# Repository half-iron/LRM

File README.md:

# LRM übersicht

### Ordner

- `axle_sensors` achsensoren info und firmware
- `NTiXL2` entält die python implementierung der serielle schnittstelle zur XL2 messgerät. Diesem Modul  
- `pyLRM` entält den python code notwendig für die scripts.

### Scripts

Die scripts dienen zur Bedienung der Messanlage. Die Scripts implementieren eine rehie von 
funktionen. Den Befehl `python3 scriptname.py -h` gibt Hinweise über die funktionalität und
 Anwendug der Scripts. 
 
Ein übersicht der implementierten funktionalitäten sind: 
- **xl2_device.py**: 
    - XL2 cycle power (strom aus und wieder ein)
    - XL2 test serial
    - XL2 mass <-> serial mode wechseln
    - XL2 mass mount und umount
    
- **messung.py** durchführt die Messung. Messdaten werden sowohl im XL2 wie im BBG generiert.

- **assign_tools.py**. Nach einer Messung müssen die XL2 und BBG Messdaten miteinander zugeordnet werden.

- **test_mail_logger.py** sendet einen testmail
    
- **test_axle_sensors.py** um axle sensor zu testen. ähnlich zur `messung.py` aber ohne XL2.

## Durchführung einer Messung
### Vorbereitungen

1. `pyLRM/config.py` file modifizieren falls nötig.

2. `pyLRM/passby.py` file modifizieren. Diesem File enthält die logik um die passby zu generieren. In zukunft diese änderung 
sollten in `pyLRM/config.py` durchgeführt werden durch subclassen von `passby.Passby` und neuschreiben der methode `run`

3. `pyLRM`, `NTiXL2`, Scripts und secret file auf BBG hochladen. 

### Messen

1. Stelle sicher dass den XL2 korrekt funktioniert und im serial modus ist. Benutze dafür 
den `xl2_device.py` script. z.B. mit:
    ```
    python3 xl2_device.py -test_serial
    ```
2. Starte die Messung mit  

    ```
       python3 messung.py TestMessung
    ```
    
    Den ordner `~\TestMessung` wird erstellt. Messdaten und logs sind dorthin gespeichert.
      
    Damit die messung auch nach den ssh logout weiterläuft muss den befehl in einen [screen](https://linuxize.com/post/how-to-use-linux-screen/) 
    Session  durchgeführt werden.
      
    ```bash
       screen
    ```
    Um den screen Session zu verlassen ctr-a d (detach).  
    Um den screen Session wieder zu öffnen `screen -r`
    Um den screen Session zu schliessen ctr-a k (kill).  

3. Stoppe die Messung  mit ctrl-c.
4. XL2 in mass modus bringen and mounten
    ```bash
        python3 xl2_device.py -to_mass -mount 
    ```
    
5. Daten runterladen
    - die XL2 daten befinden sich in `~\storagXL2`  
    - die messdaten (passby) befinden sich in `~\TestMessung`

6. XL2 wieder in serial modus bringen mit 
    ```bash
        python3 xl2_device.py -umount -eject
    ```

## Daten bereinigen und zuordnen

Zu diesem Zeitpunkt sind die passby daten und die XL2 daten in zwei ordner auf den PC. 

Als letzte Schritt nach einer Messung  müssen XL2 Daten und passby daten miteinander zugeordnet werden. 

Das Erfolgt nach diesem Schritten:

1. dauer von passby und XL2 aufnahmen prüfen 

2. zeit syncronisations zwischen passby und XL2 prüfen

3. XL2 aufnahmen und passby zuordnen

4. Neue ordnerstruktur herstellen 

Schritt 1 und 2 sind notwendig um Daten von oft auftretende Fehler zu Bereinigen. 
Diese Schritte werden mithilfe des `assign_tools.py` Script durchgeführt.

### Logs und passby daten analysieren 

Den notebook `visualize_axle_sensor_logs.ipynb` ist einen hilfmittel/Beispiel wie log Daten analysiert werden können.  
Den notebook `untersuche_assignement.ipynb` ist einen hilfmittel/Beispiel wie die Zuordnung untersucht werden kann.
  
## Ideen zur Verbesserungen

- Viele Probleme entstehen bei der Schnittstellen zum XL2 Gerät. Eine mögliche Verbesserung wäre
 die Messung nur einmal zu starten und entsprechend nur einmal stoppen. Damit wird nur ein XL2 filesatz generiert. Audiofiles werden aber dann gross
(XL2 gerät erstellt neue Files nach einer bestimmte grösse). Nur im postprocessing (assign) verden dann für die geloggte Vorbeifahrten (passby)  XL2 log und audiofiles ausgeschnitten.
**Wichtig**:
    - sync zeit Zwischen XL2 und passby(BBG) für jeden passby abfragen!
    - Messung trotzem jeden Tag neustarten damit log nicht zu gross werden un um fehler zu vermeiden.
    - Die Messung muss nicht den ganzen Tag laufen. In Zeiten ohne Verkehr (Nacht) sollte die Messung nicht laufen. 
        Zu dieser Zeiten XL2 ausschalten (mit relay), damit spart man Akku und den XL2 gerät wird resettet (Trägt zur stabilität der Messung zu). 
        Dazu können auch daten abgeholt werden. 
    - Aufpassen, kritische punkt im XL2 setum ist immer die Wahl des Messprofil.

- Alggemeine Programmierungs Verbesserungen:
    - NTiXL2 schnittstelle
    - passby module und passby class verbessern
    - Scripts verbessern. Vor allem das Argument parsing mit argparsing und die dazugehörige Dokumentation verbessern (wie im assign.py script)

- BBG: 
    - erstellen eines device tree overlay für den Relay.
    - Akku Spannung messen. Den PCB wäre dafür vorgesehn. Wobei dass problem ist dass den ADC nicht korrekt geschütz wurde. 
    Vielleicht eine bessere Lösung ist einen externen ADC (über I2C) zu wervenden. 
    Groove Module implementieren das schon und sind sehr einfach zu integrieren.  
    - Temperatur und feuchtigkeit messen. Wieder mit einen GrooveModul über I2C.

- Batterien für achszäler: Bohrmaschinen Batterien, eine genauere Messung des stromverbrauch ist zu machen.

- Mechanisches:
    - Dichtigkeit und betriebstemperaturen der Kisten prüfen 
    - Laser Lichtsensor alignement prüfen. Marke auf lichtsensor zeichen damit man sicher stellt dass den laser aligned ist.
    - Akkuverbindungsbox und Akkukabeln verbessern (Dichtigkehit und Srösse)
    -

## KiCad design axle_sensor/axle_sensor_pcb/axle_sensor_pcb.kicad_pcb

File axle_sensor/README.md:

## Grundlage
Ein Achssensor besteht grundsätzlich aus 3 bestandteile:
- Lichtschranke (LS). Die LS hat einen  Analoge output:
    - 10V => logical 1, wenn abgedekt (Rad steht im Sicht)
    - 0V => logical 0, wenn frei (freie Sicht)
- Mikrocontroller msp432 (MCU)
- XEee Radio Modul (XBee)

### Software idee 
Den Achzähler ist als State Maschine modelliert. 

**Zustände:**
1. IDLE: Setup und stromsparmodus. Die Transition  zu diesem Zustand erfolgt 
anhand einen Xbee pin Status.
2. AXLE_ON
3. AXLE_OFF
4. AXLE_ERR

**Intergrund 2kHz ISR, Low pass filter**   

    Der MCU tastet den LS Output, deren Wert `x_i` entweder 0 oder 1  ist, mit 2kHz ab. 
    Aus diesen Werte wird eine Summe aus die letzten  `sum_len` gelesen Werte gebildet `sum = Summe x_i`.
    Dazu wird in jeden Zustand ein counter `cnt` incrementiert mit 2kHZ takt.
     
**Transitions und actions**
- wenn `sum>(sum_len-threshold_ON)`: AXLE_OFF->AXLE_ON. Dann set `axle_off_time=cnt` dann set `cnt=0`
- wenn `sum<threshold_OFF`: AXLE_ON->AXLE_OFF. Dann  send msg AXLE mit`axle_off_time` und `axle_on_time=cnt` dann set `cnt=0`
- wenn `cnt>threshold_ERR`: AXLE_ON->AXLE_ERR. Dann  send msg AXLE_ERR mit`axle_off_time` 
- wenn `sum<threshold_OFF`: AXLE_ERR->AXLE_OFF. Dann set  `cnt=0`

Mehr Informationen im Code

### Einstellungen

Die State Maschine kann mit 4 parameter beeinflusst werden: `threshold_ERR,threshold_ON,threshold_OFF,sum_len`

##PrintedCircuitBoard (PCB)
Alle pcb sowohl für den axle_sensor wie für den BBG  wurden mirt KiCad hersetllt.

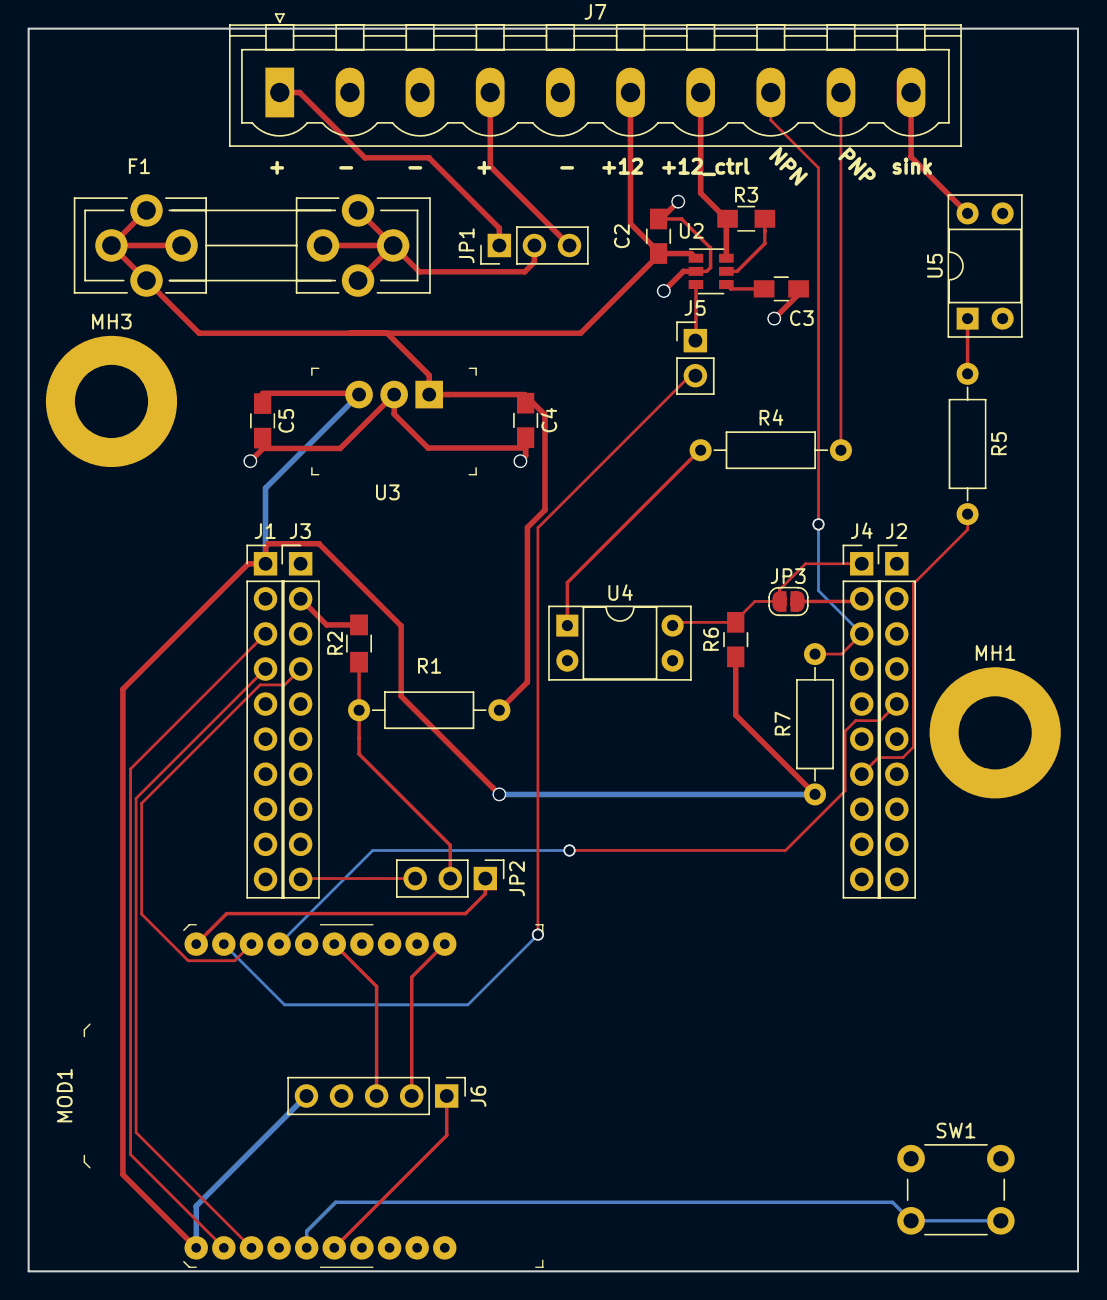
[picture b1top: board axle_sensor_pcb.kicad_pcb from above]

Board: 2 copper layers, 76.0 x 90.0 mm, 30 parts (0 on the bottom side), 30 nets.

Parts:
C2: 1u; C_0805_HandSoldering
C3: 0.001u; C_0805_HandSoldering
C4: 10u; C_0805_HandSoldering
C5: 22u; C_0805_HandSoldering
F1: Fuse; Fuseholder5x20_horiz_open_universal_Type-III
J1: TI_BOOSTER_40_J1; PinHeader_1x10_P2.54mm_Vertical
J2: TI_BOOSTER_40_J2; PinHeader_1x10_P2.54mm_Vertical
J3: TI_BOOSTER_40_J3; PinHeader_1x10_P2.54mm_Vertical
J4: TI_BOOSTER_40_J4; PinHeader_1x10_P2.54mm_Vertical
J5: Conn_01x02; Pin_Header_Straight_1x02_Pitch2.54mm
J6: Conn_01x05; Pin_Header_Straight_1x05_Pitch2.54mm
J7: Screw_Terminal_01x10; PhoenixContact_MSTBVA-G_10x5.08mm_Vertical
JP1, JP2: Jumper_3_Open; Pin_Header_Straight_1x03_Pitch2.54mm
JP3: SolderJumper_2_Open; SolderJumper-2_P1.3mm_Open_RoundedPad1.0x1.5mm
MH1, MH3: MountingHole_Pad; MountingHole_5.3mm_M5_ISO7380_Pad
MOD1: XBP24-DMSIT-250_LTB; XBEE_PRO-20_THT
R1: 220k; R_Axial_DIN0207_L6.3mm_D2.5mm_P10.16mm_Horizontal
R2: 10k; R_0805_HandSoldering
R3: 1k; R_0805_HandSoldering
R4, R7: 1k; R_Axial_DIN0207_L6.3mm_D2.5mm_P10.16mm_Horizontal
R5: 220; R_Axial_DIN0207_L6.3mm_D2.5mm_P10.16mm_Horizontal
R6: 10k; C_0805_HandSoldering
SW1: SW_Push; SW_PUSH_6mm
U2: TPS22810DBVR; SOT-23-6
U3: V7805-500; 3-SIP_Module_V7805-500
U4, U5: TLP627; DIP-4_W7.62mm_Socket

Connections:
+12V: C2.2, C4.1, F1.1, J7.6, R1.1, U2.1, U3.1
/A0: J3.10, JP2.3
/NPN: J4.3, J7.8, R7.2
/P2.3: J4.7, R5.2
/P2.7: J4.1, JP3.1, R6.2, U4.4
/P4.0: J3.4, MOD1.18
/PNP: J7.9, R4.2
/RESET_MCU: J2.5, MOD1.17
/RX: J1.3, MOD1.2
/SENSOR_VCC: J7.7, R3.1, U2.6
/SHTDOWN_SENSOR: J5.2, MOD1.19
/TX: J1.4, MOD1.3
/sink: J7.10, U5.4
GND: C2.1, C3.2, C4.2, C5.2, J2.1, J3.2, J6.4, J7.2, J7.3, J7.5, MH1.1, MOD1.10, R2.2, SW1.1, U2.2, U3.2, U4.2, U4.3, U5.2, U5.3
unnamed: C3.1, U2.4
unnamed: F1.2, JP1.2
unnamed: J4.2, JP3.2
unnamed: J5.1, U2.3
unnamed: J6.1, MOD1.6
unnamed: J6.2, MOD1.11
unnamed: J6.3, MOD1.15
unnamed: J7.1, JP1.1
unnamed: J7.4, JP1.3
unnamed: JP2.1, MOD1.20
unnamed: JP2.2, R1.2, R2.1
unnamed: MOD1.5, SW1.2
unnamed: R3.2, U2.5
unnamed: R4.1, U4.1
unnamed: R5.1, U5.1
VCC: C5.1, J1.1, J6.5, MOD1.1, R6.1, R7.1, U3.3

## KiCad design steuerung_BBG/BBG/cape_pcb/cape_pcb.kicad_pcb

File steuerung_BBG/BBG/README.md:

#Schritte um das BBG zu einrichten  

Stand 22.10.2018  

[Allgemeine BBG info](http://wiki.seeedstudio.com/BeagleBone_Green/)

1. sd karte vorbereiten  

    - BBG ist mit der image **image_name** *bone-debian-9.5-iot-armhf-2018-10-07-4gb* aufgerüstet.  [Download BBG image](https://beagleboard.org/latest-images).  
    Ich wervende immer iot image. 
    Teste sha256 checksum mit `sha256sum image_name.img.xz`.

    - Entpacke image:
    
        `xz -d image_name.img.xz > image_name.img`

    - Finde Sd-Karte name und brenne image auf Sd-Karte mit **karte_name**:
        ```bash
          sudo dd bs=4M if=image_name.img of=karte_name status=progress conv=fsync 
         ```
2. Allgemeines:  
    - Password wechseln
        ```bash
        passwd 
        ```
    - Update and upgrade
    - Grow sd card partition.  
    Die sd Karte hat nach dem brennen eine Partition grösse von ca 4GB. Um die Partition auf die 
    ganze sd-Karte grösse zu strecken diesem script durchführen.
         ```
          sudo /opt/scripts/tools/grow_partition.sh
         ```
        dann reboot. [Vertiefung](https://elinux.org/Beagleboard:Expanding_File_System_Partition_On_A_microSD)

3. Setup static ip.  
    Debian verwendet `connman`als network manager. Für weitere info sich an den manual wenden.
    Grundsätzlich funktioniert das einrichten des statische ip  wie folgt:  
    - Finde de service Name **ser_name** des ethernet network service.  
    
         ```
         sudo connmanctl services  
         
         ```  
         z.B: in meinem fall ist ser_name  **ethernet_84eb189c0c9e_cable**  
     
    - dann diesem Befehl eingeben
        ```
        connmanctl config ethernet_84eb189c0c9e_cable --ipv4 manual 192.168.5.5 255.255.255.0 192.168.5.1 --nameservers 8.8.8.8
        ```

4. ssh Tunnel einrichten. (im unterordner erklärt) 

9. Einrichten des UART für den Xbee. damit die UART Nummer 4 Schnittstelle aktiviert wird muss den korrekten device tree overlay geladen werden.  
Da erfolgt durch das modifizieren des uEnv.txt file an den Punkt `###Custom Cape`
    ```
    ###Custom Cape
    dtb_overlay=/lib/firmware/BB-UART4-00A0.dtbo
    ###
    ```
    Als Referenz benütze den abgelegte uEnv.txt File.

10. XL2 udev rules einrichten und fstab Zeile einfügen.  

    Den Abgelegte file `50-usb-XL2slm.rules` im `/etc/udev/rules.d/` copieren.
    Udev restarten mit `sudo udevadm control --reload-rules && udevadm trigger`.
      
    Zum fstab file `/etc/fstab` füge Zeile hinzu (prüfe UUID! mit `blkid`)   
    `UUID=9016-4EF8  /home/debian/storageXL2  vfat defaults,nofail,user,noauto  0  0`  
    
    Nach die udev Einstellungen sollte den XL2:  
     - wenn in serial modus, mit device name `/dev/XL2serial` erkennt werden. 
     - wenn in mass storage modus, sollte ein Disk auftauchen mit name `/dev/XL2storage` 
    
    Dank fstab das mounten sollte mit `mount storageXL2` erscheinen.   
    Umounten sollte mit `umount storageXL2` erscheinen. 
    Eject mit `eject /dev/XL2storage`

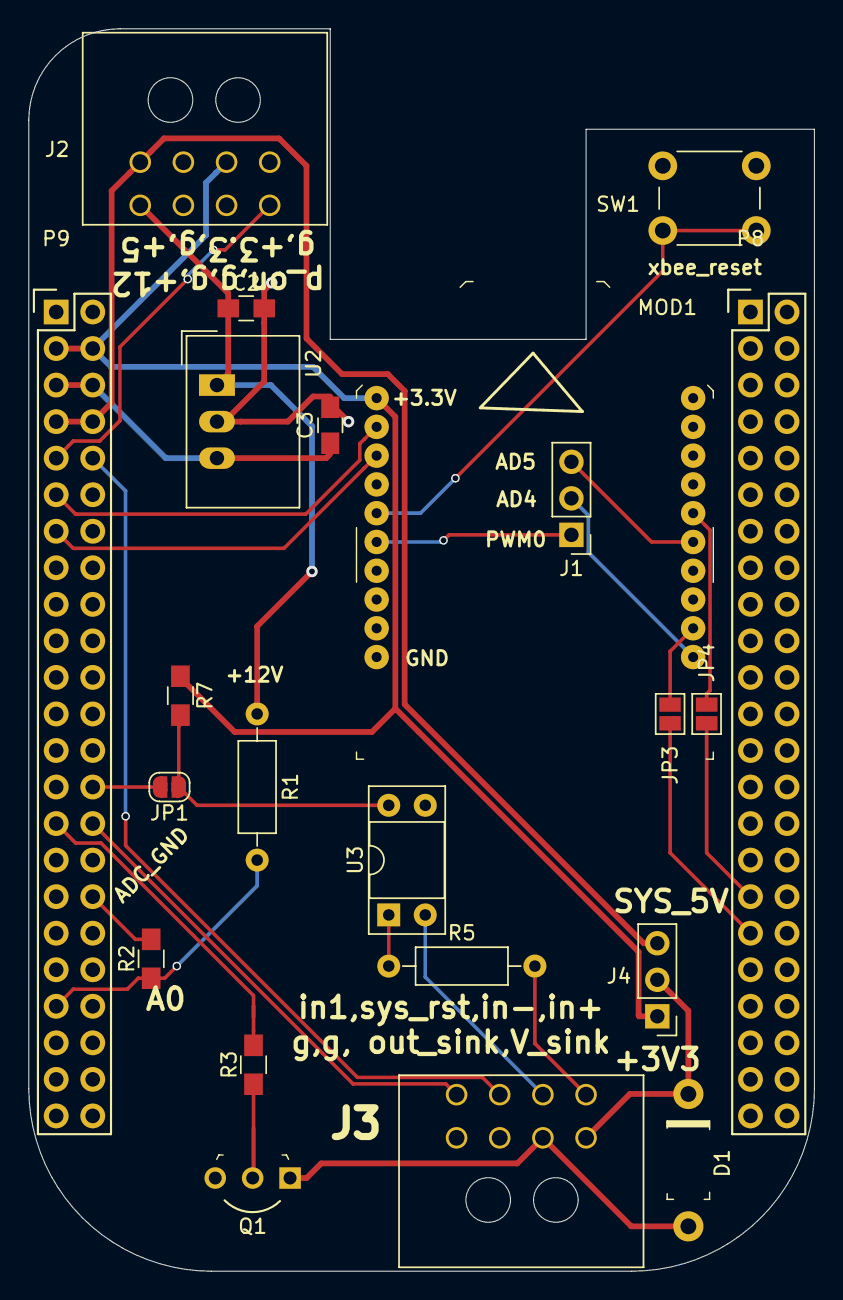
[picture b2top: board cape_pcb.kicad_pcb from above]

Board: 2 copper layers, 54.6 x 86.4 mm, 22 parts (0 on the bottom side), 29 nets.

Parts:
C2, C3: 22u; C_0805_HandSoldering
D1: 1N4001-G; DO-41
J1, J4: Conn_01x03; Socket_Strip_Straight_1x03_Pitch2.54mm
J2, J3: Conn_01x08; Molex_Microfit3_Header_02x04_Angled_43045-080x
JP1: Jumper_2_Open; SolderJumper-2_P1.3mm_Open_RoundedPad1.0x1.5mm
JP3, JP4: Jumper_2_Open; SolderJumper-2_P1.3mm_Open_Pad1.0x1.5mm
MOD1: XBP24-DMSIT-250_LTB; XBEE_PRO-20_THT
P8, P9: BeagleBone_Black_Header; Socket_BeagleBone_Black
Q1: BC33740TA; TO-92-3_Formed_Leads
R1: 220k; R_Axial_DIN0207_L6.3mm_D2.5mm_P10.16mm_Horizontal
R2, R7: 10k; R_0805_HandSoldering
R3: 560; R_0805_HandSoldering
R5: 220; R_Axial_DIN0207_L6.3mm_D2.5mm_P10.16mm_Horizontal
SW1: SW_Push; SW_PUSH_6mm
U2: TSR_1-2450; DCDC-Conv_TRACO_TSR-1
U3: TLP627; DIP-4_W7.62mm_Socket

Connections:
+3V3: J2.3, J4.1, MOD1.1, P9.3, P9.4, R7.1
+5V: C3.1, P9.5, P9.6, U2.3
+12V: C2.1, J2.5, R1.1, U2.1
/in1+: J3.5, R5.2
/in1-: J3.6, U3.2
A0: P9.39, R1.2, R2.1
GNDA_ADC: P9.34, R2.2
GNDD: C2.2, C3.2, J2.2, J2.4, J2.6, J2.7, J3.3, J3.4, MOD1.10, P8.1, P8.2, P9.1, P9.2, P9.43, P9.44, P9.45, P9.46, Q1.3, SW1.1, U2.2, U3.3
IN0: JP1.2, P9.28
IN1: J3.8, P9.30
unnamed: D1.A, J3.2, Q1.1
unnamed: D1.K, J3.1, J4.2
unnamed: J1.1, MOD1.6
unnamed: J1.2, MOD1.11
unnamed: J1.3, MOD1.15
unnamed: JP1.1, R7.2, U3.4
unnamed: JP3.1, MOD1.12
unnamed: JP4.1, MOD1.16
unnamed: MOD1.5, SW1.2
unnamed: Q1.2, R3.1
unnamed: R5.1, U3.1
OUT0: P9.29, R3.2
PWR_BUT: J2.8, P9.9
SYS_5V: J2.1, J4.3, P9.7, P9.8
SYS_RESETN: J3.7, P9.10
UART4_CTS: JP3.2, P8.35
UART4_RTS: JP4.2, P8.33
UART4_RXD: MOD1.2, P9.11
UART4_TXD: MOD1.3, P9.13

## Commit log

2018-10-17 Added firmware for axle sensor.
2018-10-17 Neue Configurationsfiles für Xbee. README updated.
2018-10-17 axle sensor stuff working. Rest broken.
2018-10-22 Add arguments to test_axle_sensor.py: - Arguments for setting up axle sensors - Other general Arguments
    Other:
    - Improved logging formatter
2018-11-12 added xl2_device.py script. The script serve as rool for mounting, umounting xl2 devices. added udev rules for xl2_device.py removed unused old files
2018-11-12 passby name modification
2018-11-12 added NTiXL2 module source to project
2018-11-12 add messung.py
2018-11-27 many changes
2018-11-27 documentation
2018-11-27 documentation und assign_tools
2018-11-28 documentation changes
2018-12-01 axle sensor documentation
2018-12-01 assignement script done
2019-07-01 Tippfehler
